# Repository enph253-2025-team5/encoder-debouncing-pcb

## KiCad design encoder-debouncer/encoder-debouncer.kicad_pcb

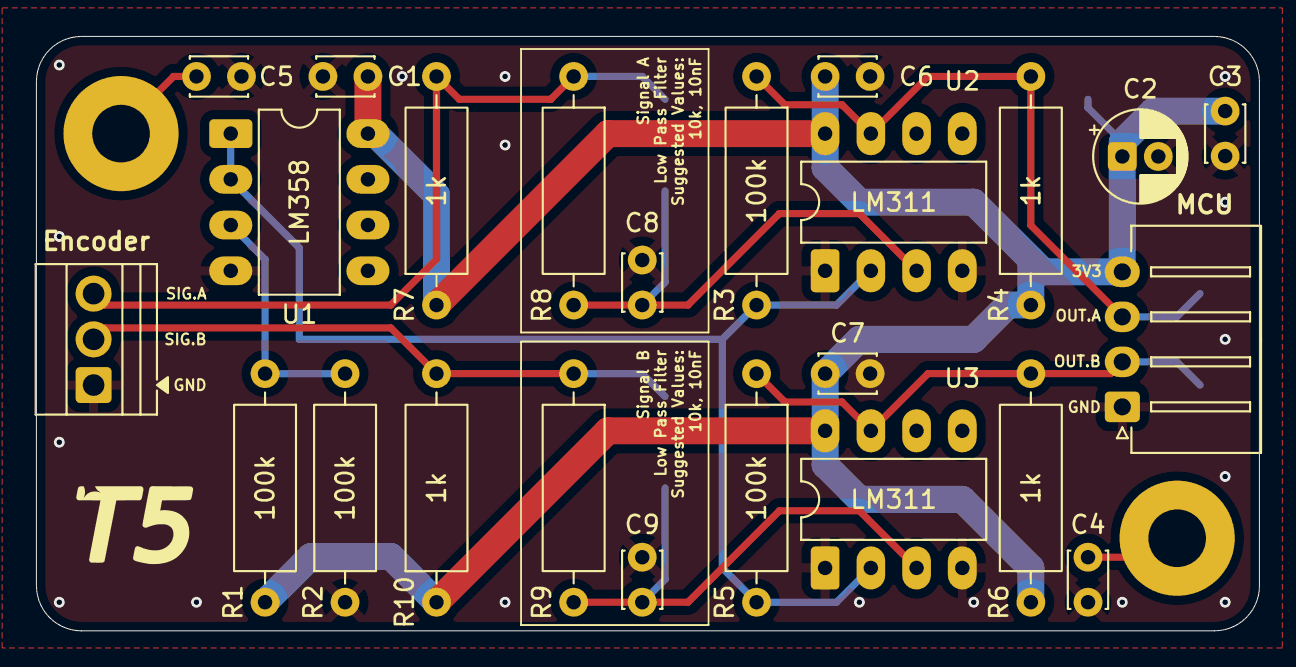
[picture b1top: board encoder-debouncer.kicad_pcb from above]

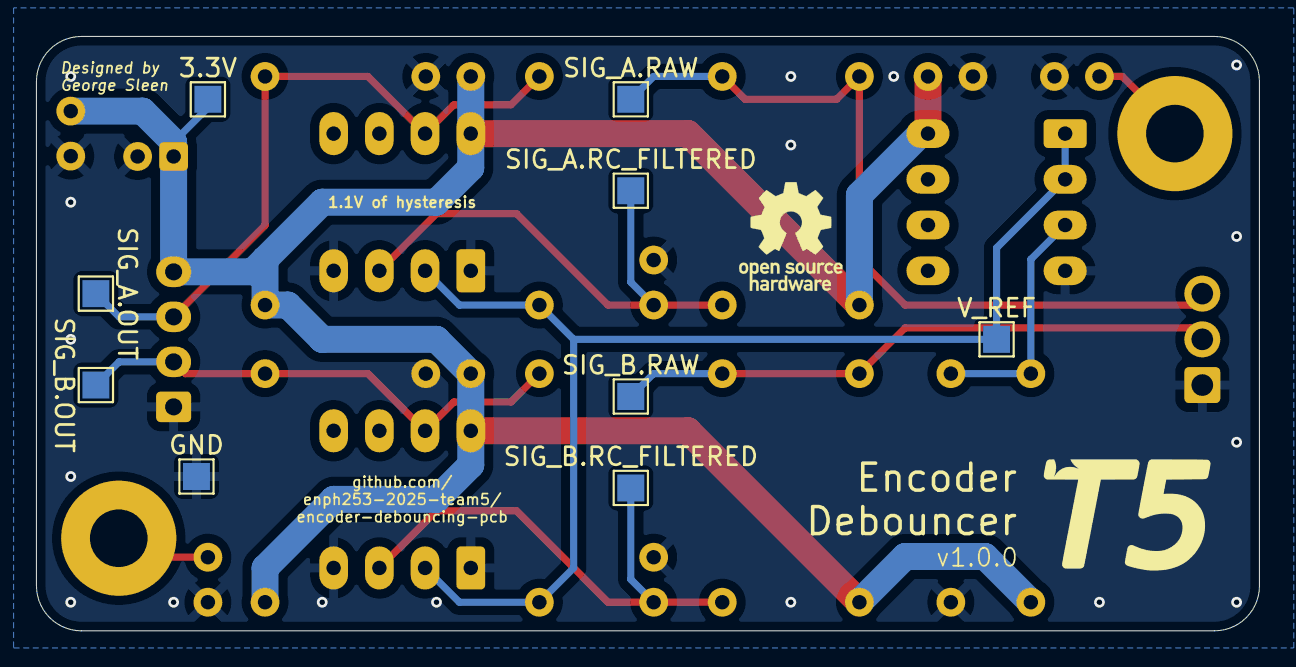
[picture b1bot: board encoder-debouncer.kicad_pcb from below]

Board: 2 copper layers, 67.9 x 33.0 mm, 37 parts (10 on the bottom side), 12 nets.

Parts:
C1, C3, C4, C5, C6, C7: 100nF; C_Disc_D3.0mm_W2.0mm_P2.50mm
C2: 10uF; CP_Radial_D5.0mm_P2.00mm
C8, C9: 10nF; C_Disc_D3.0mm_W2.0mm_P2.50mm
H1, H2: M3_PTH; MountingHole_3.2mm_M3_Pad
J1: Encoder; TerminalBlock_Xinya_XY308-2.54-3P_1x03_P2.54mm_Horizontal
J2: MCU; JST_XH_S4B-XH-A-1_1x04_P2.50mm_Horizontal
R1, R2, R3, R5: 100k; R_Axial_DIN0309_L9.0mm_D3.2mm_P12.70mm_Horizontal
R4, R6, R7, R10: 1k; R_Axial_DIN0309_L9.0mm_D3.2mm_P12.70mm_Horizontal
R8, R9: 10k; R_Axial_DIN0309_L9.0mm_D3.2mm_P12.70mm_Horizontal
S1: Logo; ENPH253_Logo_Small
S2: Logo; ENPH253_Logo
TP1: SIG_A.RAW; TestPoint_Pad_1.5x1.5mm
TP2: SIG_A.RC_FILTERED; TestPoint_Pad_1.5x1.5mm
TP3: SIG_A.OUT; TestPoint_Pad_1.5x1.5mm
TP4: V_REF; TestPoint_Pad_1.5x1.5mm
TP5: SIG_B.RAW; TestPoint_Pad_1.5x1.5mm
TP6: SIG_B.RC_FILTERED; TestPoint_Pad_1.5x1.5mm
TP7: SIG_B.OUT; TestPoint_Pad_1.5x1.5mm
TP8: 3.3V; TestPoint_Pad_1.5x1.5mm
TP9: GND; TestPoint_Pad_1.5x1.5mm
U1: LM358; DIP-8_W7.62mm_LongPads
U2, U3: LM311; DIP-8_W7.62mm_LongPads

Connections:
+3.3V: C1.1, C2.1, C3.1, C6.1, C7.1, J2.4, R1.2, R4.1, R6.1, R7.1, R10.1, TP8.1, U1.8 (V+), U2.8 (V+), U3.8 (V+)
/RC low pass network A/V_OUT: C8.1, R8.2, TP2.1, U2.3 (-)
/RC low pass network B/V_OUT: C9.1, R9.2, TP6.1, U3.3 (-)
/SIG_A.IN: J1.3, R7.2, R8.1, TP1.1
/SIG_A.OUT: J2.3, R3.1, R4.2, TP3.1, U2.7
/SIG_B.IN: J1.2, R9.1, R10.2, TP5.1
/SIG_B.OUT: J2.2, R5.1, R6.2, TP7.1, U3.7
/V_REF: R3.2, R5.2, TP4.1, U1.1, U1.2 (-), U2.2 (+), U3.2 (+)
GND: C1.2, C2.2, C3.2, C4.2, C5.2, C6.2, C7.2, C8.2, C9.2, J1.1, J2.1, R2.1, TP9.1, U1.4 (V-), U2.1 (EMIT), U2.4 (V-), U3.1 (EMIT), U3.4 (V-)
unnamed: C4.1, H1.1
unnamed: C5.1, H2.1
unnamed: R1.1, R2.2, U1.3 (+)

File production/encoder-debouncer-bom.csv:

"Value","Qty","Reference","Footprint"
"MCU","1","J2","GS_Connectors:JST_XH_S4B-XH-A-1_1x04_P2.50mm_Horizontal"
"Encoder","1","J1","TerminalBlock:TerminalBlock_Xinya_XY308-2.54-3P_1x03_P2.54mm_Horizontal"
"LM358","1","U1","Package_DIP:DIP-8_W7.62mm_LongPads"
"10uF","1","C2","Capacitor_THT:CP_Radial_D5.0mm_P2.00mm"
"100k","4","R1,R2,R3,R5","Resistor_THT:R_Axial_DIN0309_L9.0mm_D3.2mm_P12.70mm_Horizontal"
"1k","4","R4,R6,R7,R10","Resistor_THT:R_Axial_DIN0309_L9.0mm_D3.2mm_P12.70mm_Horizontal"
"10k","2","R8,R9","Resistor_THT:R_Axial_DIN0309_L9.0mm_D3.2mm_P12.70mm_Horizontal"
"100nF","6","C1,C3,C4,C5,C6,C7","Capacitor_THT:C_Disc_D3.0mm_W2.0mm_P2.50mm"
"10nF","2","C8,C9","Capacitor_THT:C_Disc_D3.0mm_W2.0mm_P2.50mm"
"LM311","2","U2,U3","Package_DIP:DIP-8_W7.62mm_LongPads"

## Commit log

2025-07-09 Remove previous production outputs and rename project
2025-07-09 Finish new layout
2025-07-09 Name housekeeping
2025-07-09 Create production outputs
